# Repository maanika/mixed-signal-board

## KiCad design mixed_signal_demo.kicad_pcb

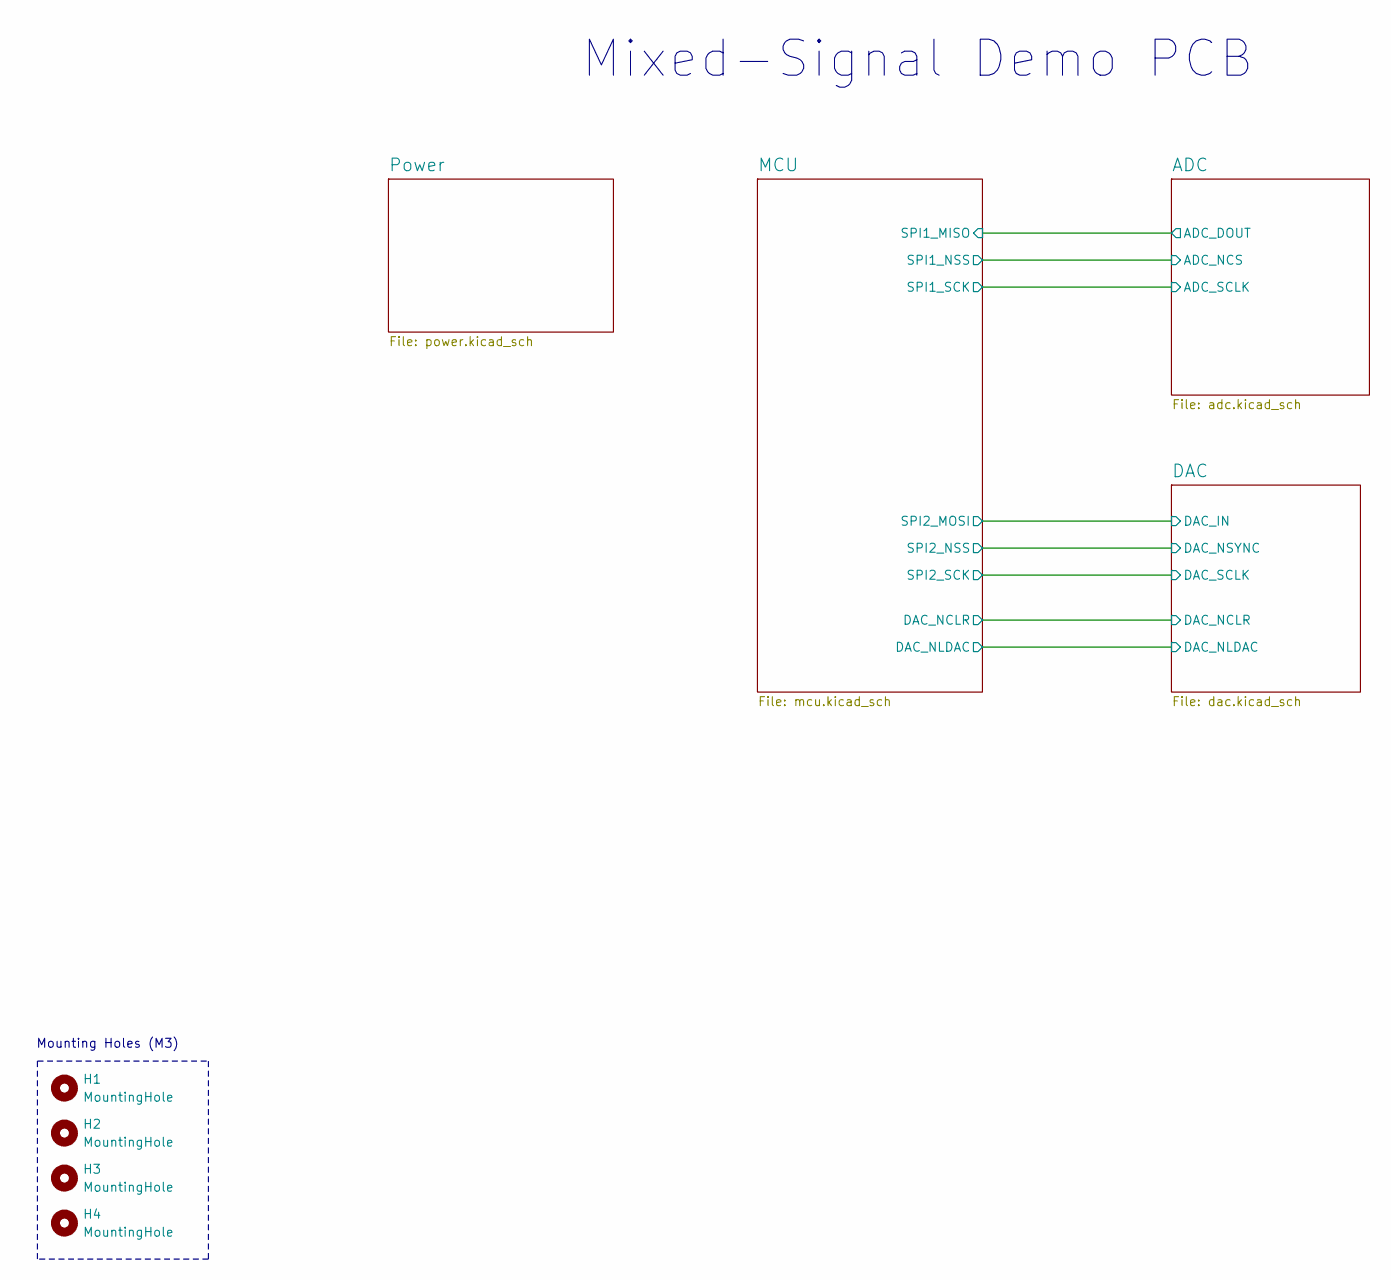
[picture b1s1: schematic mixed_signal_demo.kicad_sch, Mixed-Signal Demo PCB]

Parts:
H1, H2, H3, H4: MountingHole; MountingHole_3.2mm_M3

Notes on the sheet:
Mixed-Signal Demo PCB
Mounting Holes (M3)

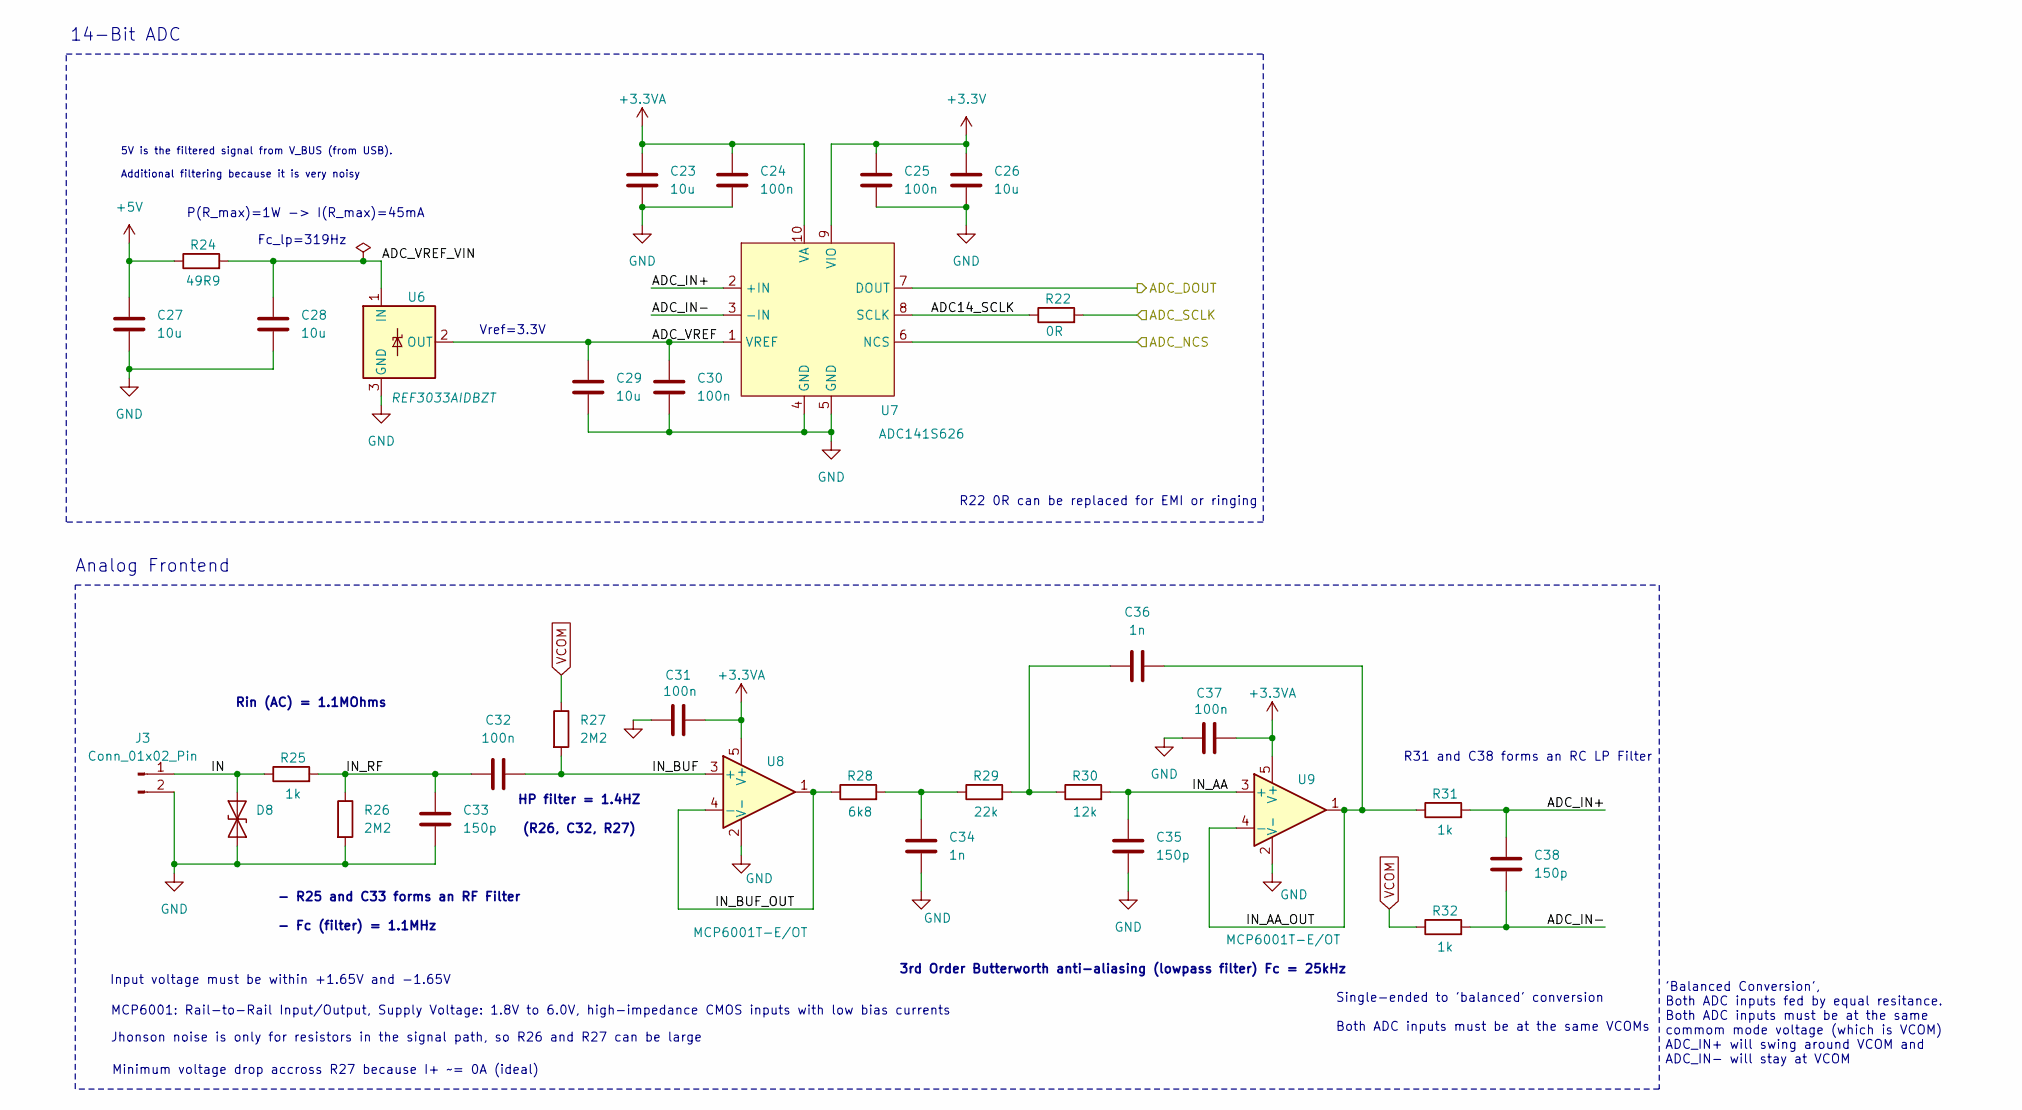
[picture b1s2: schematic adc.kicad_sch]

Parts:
C23, C26, C27, C28, C29: 10u; C_0603_1608Metric
C24, C25, C30, C31, C32, C37: 100n; C_0402_1005Metric
C33, C35, C38: 150p; C_0402_1005Metric
C34, C36: 1n; C_0402_1005Metric
D8: PESD3V3L1BA; PESD3V3L1BA_SOD-323
J3: Conn_01x02_Pin; PinHeader_1x02_P2.54mm_Vertical
R22: 0R; R_0603_1608Metric
R24: 49R9; R_0805_2012Metric
R25, R31, R32: 1k; R_0402_1005Metric
R26, R27: 2M2; R_0402_1005Metric
R28: 6k8; R_0402_1005Metric
R29: 22k; R_0402_1005Metric
R30: 12k; R_0402_1005Metric
U6: REF3033AIDBZT; SOT-23
U7: ADC141S626; VSSOP-10_3x3mm_P0.5mm
U8, U9: MCP6001T-E/OT; SOT-23-5

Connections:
+3.3V: C25.1, C26.1, U7.9 (VIO); also elsewhere on the board
+3.3VA: C23.1, C24.1, C31.2, C37.2, U7.10 (VA), U8.5 (V+), U9.5 (V+); also elsewhere on the board
+5V: C27.2, R24.1; also elsewhere on the board
/ADC/ADC14_SCLK: R22.1, U7.8 (SCLK)
/ADC/ADC_DOUT: U7.7 (DOUT); also elsewhere on the board
/ADC/ADC_IN+: C38.1, R31.2, U7.2 (+IN)
/ADC/ADC_IN-: C38.2, R32.2, U7.3 (-IN)
/ADC/ADC_NCS: U7.6 (NCS); also elsewhere on the board
/ADC/ADC_SCLK: R22.2; also elsewhere on the board
/ADC/ADC_VREF: C29.2, C30.2, U6.2 (OUT), U7.1 (VREF)
/ADC/ADC_VREF_VIN: C28.1, R24.2, U6.1 (IN)
/ADC/IN: D8.1 (A1), J3.1, R25.1
/ADC/IN_AA: C35.1, R30.2, U9.3 (+)
/ADC/IN_AA_OUT: C36.2, R31.1, U9.1, U9.4 (-)
/ADC/IN_BUF: C32.2, R27.2, U8.3 (+)
/ADC/IN_BUF_OUT: R28.1, U8.1, U8.4 (-)
/ADC/IN_RF: C32.1, C33.1, R25.2, R26.1
GND: C23.2, C24.2, C25.2, C26.2, C27.1, C28.2, C29.1, C30.1, C31.1, C33.2, C34.2, C35.2, C37.1, D8.2 (A2), J3.2, R26.2, U6.3 (GND), U7.4 (GND), U7.5 (GND), U8.2 (V-), U9.2 (V-); also elsewhere on the board
unnamed: C34.1, R28.2, R29.1
unnamed: C36.1, R29.2, R30.1
VCOM: R27.1, R32.1; also elsewhere on the board

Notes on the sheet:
14-Bit ADC
HP filter = 1.4HZ (R26, C32, R27)
'Balanced Conversion', Both ADC inputs fed by equal resitance. Both ADC inputs must be at the same commom mode voltage (which is VCOM) ADC_IN+ will swing around VCOM and ADC_IN- will stay at VCOM
MCP6001: Rail-to-Rail Input/Output, Supply Voltage: 1.8V to 6.0V, high-impedance CMOS inputs with low bias currents
Rin (AC) = 1.1MOhms
Vref=3.3V
P(R_max)=1W -> I(R_max)=45mA
R31 and C38 forms an RC LP Filter
Analog Frontend
Fc_lp=319Hz
3rd Order Butterworth anti-aliasing (lowpass filter) Fc = 25kHz
Single-ended to 'balanced' conversion Both ADC inputs must be at the same VCOMs
5V is the filtered signal from V_BUS (from USB). Additional filtering because it is very noisy
Minimum voltage drop accross R27 because I+ ~= 0A (ideal)
R22 0R can be replaced for EMI or ringing
Input voltage must be within +1.65V and -1.65V
- R25 and C33 forms an RF Filter - Fc (filter) = 1.1MHz
Jhonson noise is only for resistors in the signal path, so R26 and R27 can be large

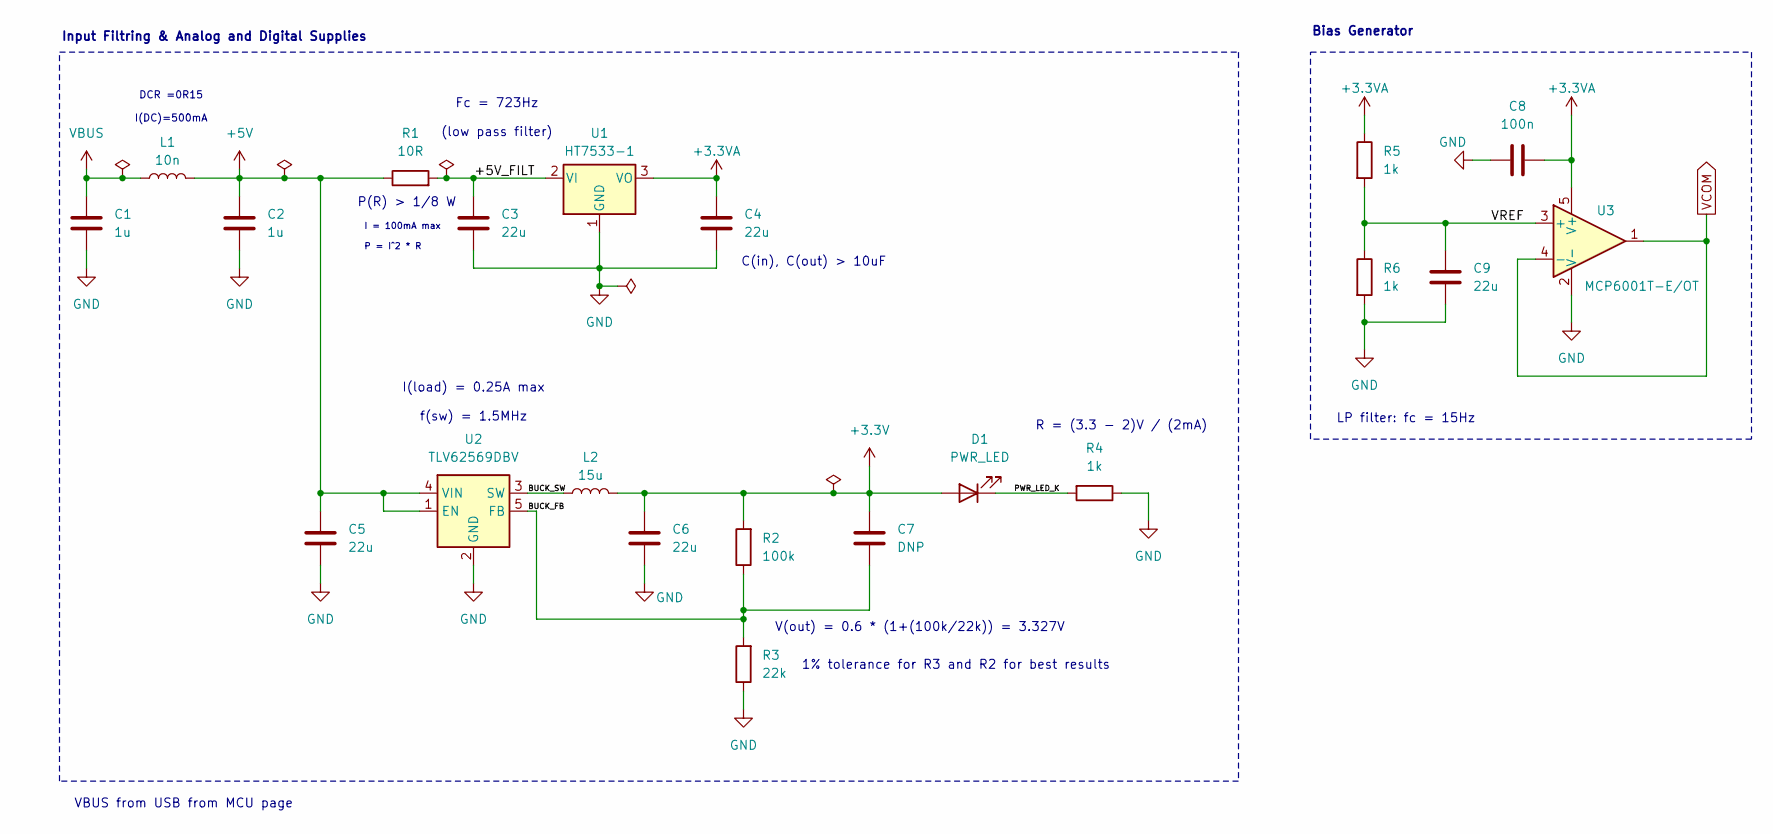
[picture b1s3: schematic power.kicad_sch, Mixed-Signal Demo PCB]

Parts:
C1, C2: 1u; C_0603_1608Metric
C3, C4, C5, C6, C9: 22u; C_0805_2012Metric
C7: DNP; C_0402_1005Metric
C8: 100n; C_0402_1005Metric
D1: PWR_LED; LED_0603_1608Metric
L1: 10n; L_0603_1608Metric
L2: 15u; L_Coilcraft_XAL4020-XXX
R1: 10R; R_0805_2012Metric
R2: 100k; R_0402_1005Metric
R3: 22k; R_0402_1005Metric
R4, R5, R6: 1k; R_0402_1005Metric
U1: HT7533-1; SOT-89-3
U2: TLV62569DBV; SOT-23-5
U3: MCP6001T-E/OT; SOT-23-5

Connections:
+3.3V: C6.1, C7.1, D1.2 (A), L2.2, R2.2; also elsewhere on the board
+3.3VA: C4.1, C8.2, R5.1, U1.3 (VO), U3.5 (V+); also elsewhere on the board
+5V: C2.1, C5.1, L1.2, R1.1, U2.1 (EN), U2.4 (VIN); also elsewhere on the board
/Power/+5V_FILT: C3.1, R1.2, U1.2 (VI)
/Power/BUCK_FB: C7.2, R2.1, R3.2, U2.5 (FB)
/Power/BUCK_SW: L2.1, U2.3 (SW)
/Power/PWR_LED_K: D1.1 (K), R4.2
/Power/VREF: C9.1, R5.2, R6.1, U3.3 (+)
GND: C1.2, C2.2, C3.2, C4.2, C5.2, C6.2, C8.1, C9.2, R3.1, R4.1, R6.2, U1.1 (GND), U2.2 (GND), U3.2 (V-); also elsewhere on the board
VBUS: C1.1, L1.1; also elsewhere on the board
VCOM: U3.1, U3.4 (-); also elsewhere on the board

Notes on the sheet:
P(R) > 1/8 W
C(in), C(out) > 10uF
DCR =0R15 I(DC)=500mA
I(load) = 0.25A max f(sw) = 1.5MHz
VBUS from USB from MCU page
V(out) = 0.6 * (1+(100k/22k)) = 3.327V
Input Filtring & Analog and Digital Supplies
LP filter: fc = 15Hz
Bias Generator
1% tolerance for R3 and R2 for best results
Fc = 723Hz (low pass filter)
I = 100mA max P = I^2 * R
R = (3.3 - 2)V / (2mA)

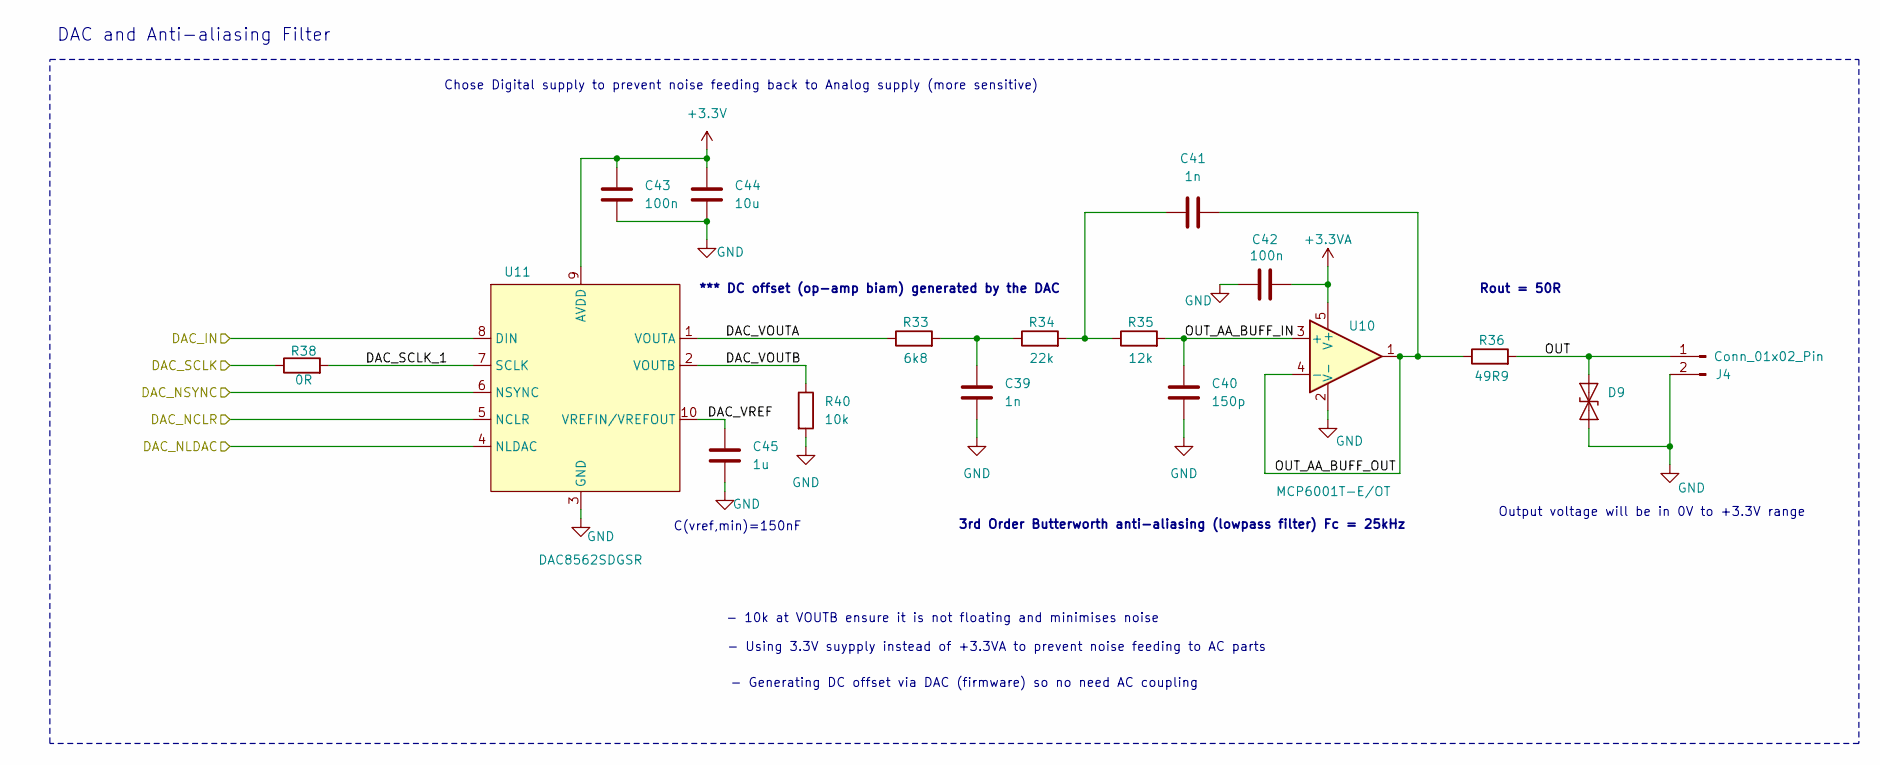
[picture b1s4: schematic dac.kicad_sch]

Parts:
C39, C41: 1n; C_0402_1005Metric
C40: 150p; C_0402_1005Metric
C42, C43: 100n; C_0402_1005Metric
C44: 10u; C_0603_1608Metric
C45: 1u; C_0603_1608Metric
D9: PESD3V3L1BA; PESD3V3L1BA_SOD-323
J4: Conn_01x02_Pin; PinHeader_1x02_P2.54mm_Vertical
R33: 6k8; R_0402_1005Metric
R34: 22k; R_0402_1005Metric
R35: 12k; R_0402_1005Metric
R36: 49R9; R_0402_1005Metric
R38: 0R; R_0603_1608Metric
R40: 10k; R_0402_1005Metric
U10: MCP6001T-E/OT; SOT-23-5
U11: DAC8562SDGSR; VSSOP-10_3x3mm_P0.5mm

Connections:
+3.3V: C43.1, C44.1, U11.9 (AVDD); also elsewhere on the board
+3.3VA: C42.2, U10.5 (V+); also elsewhere on the board
/DAC/DAC_IN: U11.8 (DIN); also elsewhere on the board
/DAC/DAC_NCLR: U11.5 (NCLR); also elsewhere on the board
/DAC/DAC_NLDAC: U11.4 (NLDAC); also elsewhere on the board
/DAC/DAC_NSYNC: U11.6 (NSYNC); also elsewhere on the board
/DAC/DAC_SCLK: R38.1; also elsewhere on the board
/DAC/DAC_SCLK_1: R38.2, U11.7 (SCLK)
/DAC/DAC_VOUTA: R33.1, U11.1 (VOUTA)
/DAC/DAC_VOUTB: R40.1, U11.2 (VOUTB)
/DAC/DAC_VREF: C45.2, U11.10 (VREFIN/VREFOUT)
/DAC/OUT: D9.1 (A1), J4.1, R36.2
/DAC/OUT_AA_BUFF_IN: C40.1, R35.2, U10.3 (+)
/DAC/OUT_AA_BUFF_OUT: C41.2, R36.1, U10.1, U10.4 (-)
GND: C39.2, C40.2, C42.1, C43.2, C44.2, C45.1, D9.2 (A2), J4.2, R40.2, U10.2 (V-), U11.3 (GND); also elsewhere on the board
unnamed: C39.1, R33.2, R34.1
unnamed: C41.1, R34.2, R35.1

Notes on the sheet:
- Generating DC offset via DAC (firmware) so no need AC coupling
*** DC offset (op-amp biam) generated by the DAC
C(vref,min)=150nF
Chose Digital supply to prevent noise feeding back to Analog supply (more sensitive)
Output voltage will be in 0V to +3.3V range
DAC and Anti-aliasing Filter
3rd Order Butterworth anti-aliasing (lowpass filter) Fc = 25kHz
- Using 3.3V suypply instead of +3.3VA to prevent noise feeding to AC parts
Rout = 50R
- 10k at VOUTB ensure it is not floating and minimises noise

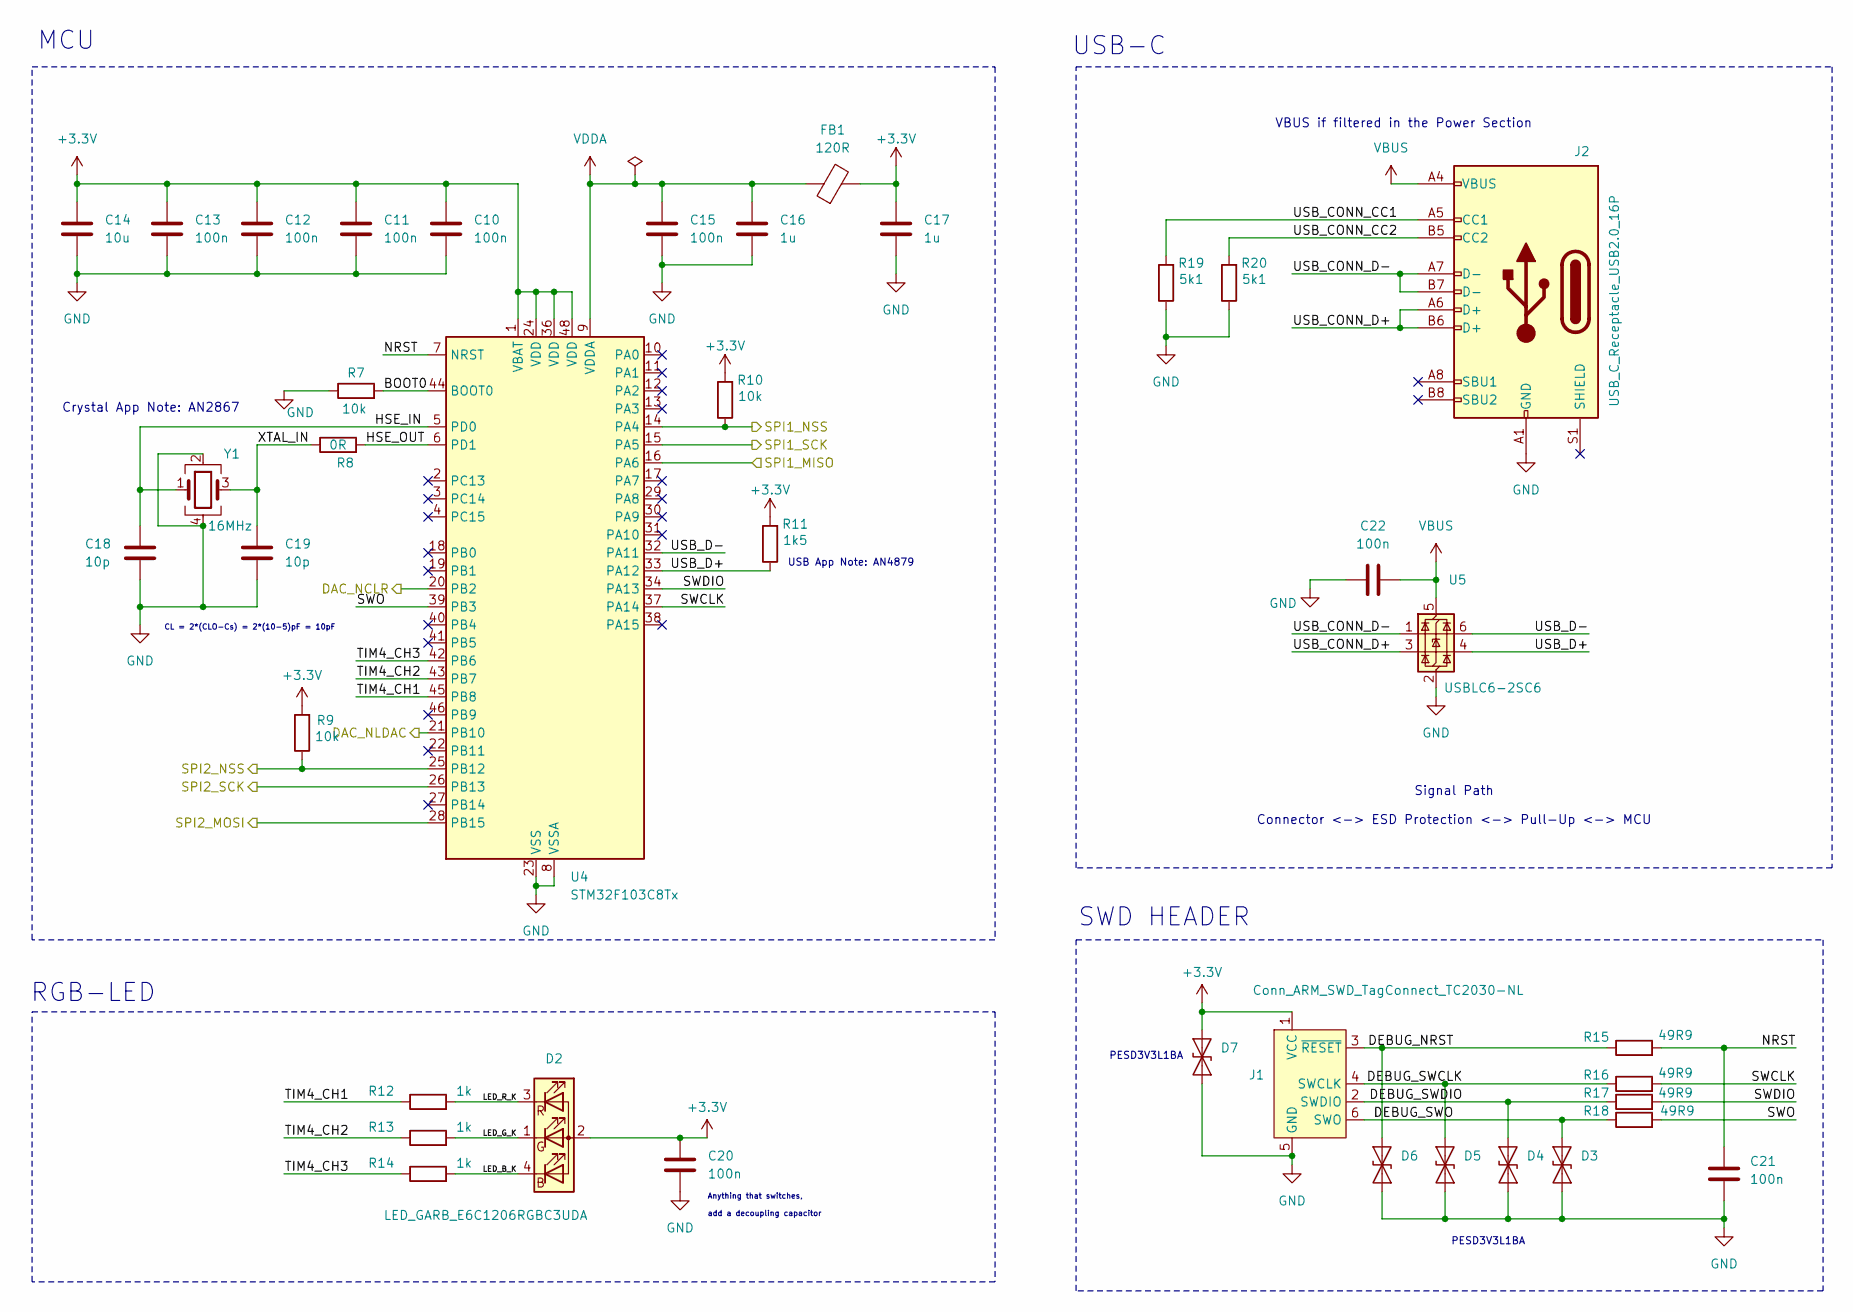
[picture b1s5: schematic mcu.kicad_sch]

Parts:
C10, C11, C12, C13, C15, C20, C21, C22: 100n; C_0402_1005Metric
C14: 10u; C_0603_1608Metric
C16, C17: 1u; C_0603_1608Metric
C18, C19: 10p; C_0402_1005Metric
D2: LED_GARB_E6C1206RGBC3UDA; LED_RGB_1206
D3, D4, D5, D6, D7: PESD3V3L1BA; PESD3V3L1BA_SOD-323
FB1: 120R; L_0603_1608Metric
J1: Conn_ARM_SWD_TagConnect_TC2030-NL; Tag-Connect_TC2030-IDC-NL_2x03_P1.27mm_Vertical
J2: USB_C_Receptacle_USB2.0_16P; USB_C_Receptacle_G-Switch_GT-USB-7010ASV
R7, R9, R10: 10k; R_0402_1005Metric
R8: 0R; R_0402_1005Metric
R11: 1k5; R_0402_1005Metric
R12, R13, R14: 1k; R_0402_1005Metric
R15, R16, R17, R18: 49R9; R_0402_1005Metric
R19, R20: 5k1; R_0402_1005Metric
U4: STM32F103C8Tx; LQFP-48_7x7mm_P0.5mm
U5: USBLC6-2SC6; SOT-23-6
Y1: 16MHz; Crystal_SMD_3225-4Pin_3.2x2.5mm

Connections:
+3.3V: C10.1, C11.1, C12.1, C13.1, C14.1, C17.1, C20.1, D2.2 (A), D7.1 (A1), FB1.2, J1.1 (VCC), R9.2, R10.2, R11.2, U4.1 (VBAT), U4.24 (VDD), U4.36 (VDD), U4.48 (VDD); also elsewhere on the board
/ADC/ADC_DOUT: U4.16 (PA6); also elsewhere on the board
/ADC/ADC_NCS: R10.1, U4.14 (PA4); also elsewhere on the board
/ADC/ADC_SCLK: U4.15 (PA5); also elsewhere on the board
/DAC/DAC_IN: U4.28 (PB15); also elsewhere on the board
/DAC/DAC_NCLR: U4.20 (PB2); also elsewhere on the board
/DAC/DAC_NLDAC: U4.21 (PB10); also elsewhere on the board
/DAC/DAC_NSYNC: R9.1, U4.25 (PB12); also elsewhere on the board
/DAC/DAC_SCLK: U4.26 (PB13); also elsewhere on the board
/MCU/BOOT0: R7.2, U4.44 (BOOT0)
/MCU/DEBUG_NRST: D6.1 (A1), J1.3 (~RESET), R15.1
/MCU/DEBUG_SWCLK: D5.1 (A1), J1.4 (SWCLK), R16.1
/MCU/DEBUG_SWDIO: D4.1 (A1), J1.2 (SWDIO), R17.1
/MCU/DEBUG_SWO: D3.1 (A1), J1.6 (SWO), R18.1
/MCU/HSE_IN: C18.1, U4.5 (PD0), Y1.1
/MCU/HSE_OUT: R8.2, U4.6 (PD1)
/MCU/LED_B_K: D2.4 (BK), R14.2
/MCU/LED_G_K: D2.1 (GK), R13.2
/MCU/LED_R_K: D2.3 (RK), R12.2
/MCU/NRST: C21.1, R15.2, U4.7 (NRST)
/MCU/SWCLK: R16.2, U4.37 (PA14)
/MCU/SWDIO: R17.2, U4.34 (PA13)
/MCU/SWO: R18.2, U4.39 (PB3)
/MCU/TIM4_CH1: R12.1, U4.45 (PB8)
/MCU/TIM4_CH2: R13.1, U4.43 (PB7)
/MCU/TIM4_CH3: R14.1, U4.42 (PB6)
/MCU/USB_CONN_CC1: J2.A5 (CC1), R19.2
/MCU/USB_CONN_CC2: J2.B5 (CC2), R20.2
/MCU/USB_CONN_D+: J2.A6 (D+), J2.B6 (D+), U5.3 (I/O2)
/MCU/USB_CONN_D-: J2.A7 (D-), J2.B7 (D-), U5.1 (I/O1)
/MCU/USB_D+: R11.1, U4.33 (PA12), U5.4 (I/O2)
/MCU/USB_D-: U4.32 (PA11), U5.6 (I/O1)
/MCU/XTAL_IN: C19.1, R8.1, Y1.3
GND: C10.2, C11.2, C12.2, C13.2, C14.2, C15.2, C16.2, C17.2, C18.2, C19.2, C20.2, C21.2, C22.1, D3.2 (A2), D4.2 (A2), D5.2 (A2), D6.2 (A2), D7.2 (A2), J1.5 (GND), J2.A1 (GND), J2.A12 (GND), J2.B1 (GND), J2.B12 (GND), R7.1, R19.1, R20.1, U4.8 (VSSA), U4.23 (VSS), U4.35 (VSS), U4.47 (VSS), U5.2 (GND), Y1.2, Y1.4; also elsewhere on the board
VBUS: C22.2, J2.A4 (VBUS), J2.A9 (VBUS), J2.B4 (VBUS), J2.B9 (VBUS), U5.5 (VBUS); also elsewhere on the board
VDDA: C15.1, C16.1, FB1.1, U4.9 (VDDA)

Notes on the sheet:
PESD3V3L1BA
Anything that switches, add a decoupling capacitor
USB App Note: AN4879
MCU
CL = 2*(CLO-Cs) = 2*(10-5)pF = 10pF
Crystal App Note: AN2867
USB-C
VBUS if filtered in the Power Section
SWD HEADER
Signal Path Connector <-> ESD Protection <-> Pull-Up <-> MCU
RGB-LED

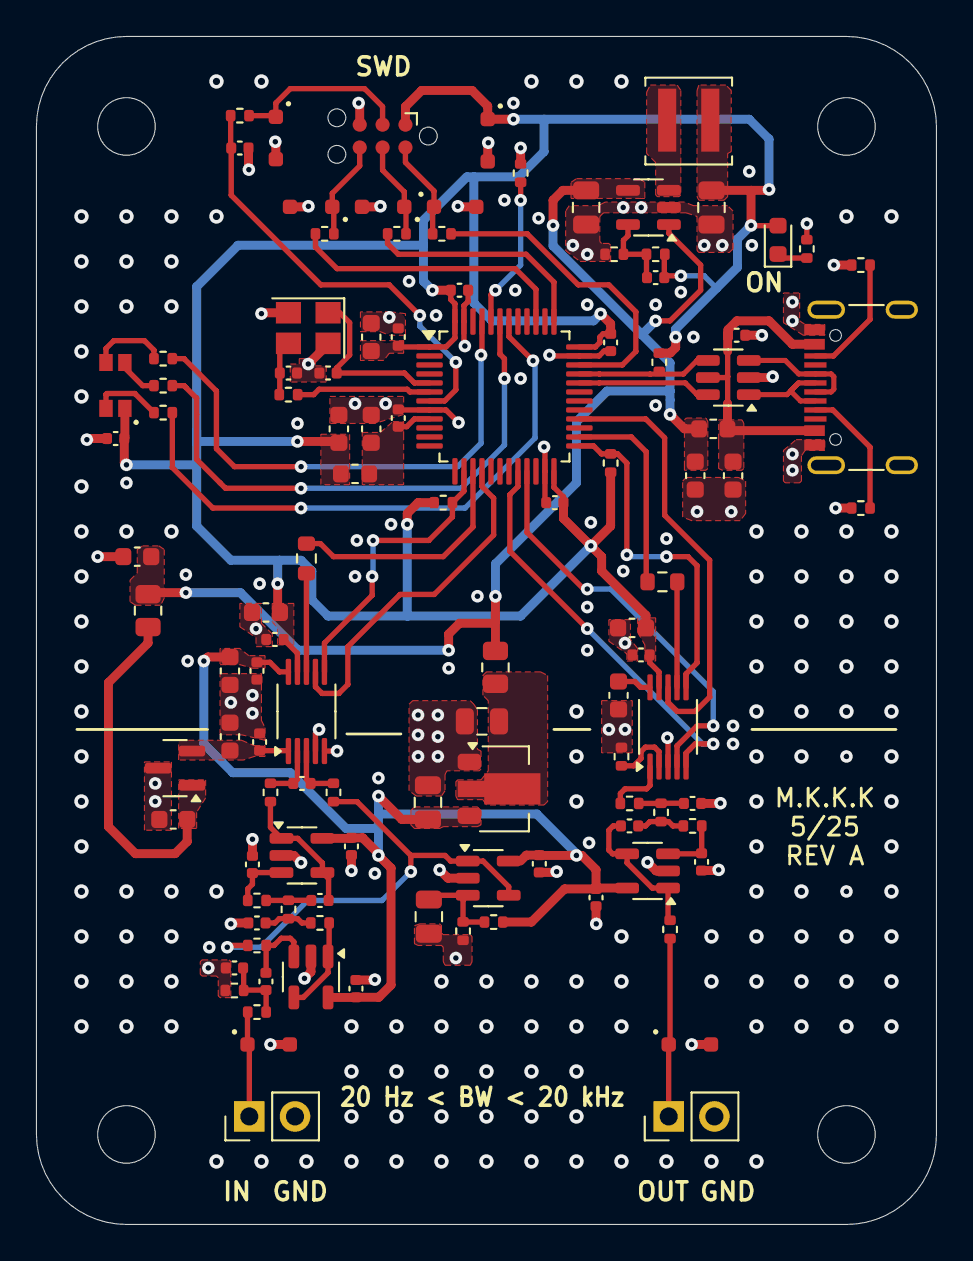
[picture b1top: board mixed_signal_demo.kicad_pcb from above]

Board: 4 copper layers, 50.0 x 66.0 mm, 113 parts (0 on the bottom side), 66 nets.

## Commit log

2025-05-20 add gitignore file
2025-05-20 Add KiCad project files
